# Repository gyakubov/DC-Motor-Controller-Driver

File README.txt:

DC Motor Controller & Driver README
===================================

This directory has the open source DC Motor Controller & Driver software, board layouts, schematics, and parts list.

For the latest updates by the original author of this project visit:
http://morgandemers.com/?page_id=444

Author: Morgan Demers

+---------+
| LICENSE |
+---------+

This work is licensed under the Creative Commons Attribution-NonCommercial-ShareAlike 3.0 Unported License. To view a copy of this license, visit http://creativecommons.org/licenses/by-nc-sa/3.0/.

+--------------+
| Introduction |
+--------------+

In the winter of 2009 I began working on a Gingery Style metal lathe, as an alternative to buying a chinese made 7x12. It was my desire to attain some casting and machining skills, and in the end to have a lathe with similar capabilities. The original Gingery design calls for cone pulleys and belt changes to get varying speeds with no compensation for load. As I have a background in Computer Engineering, I thought it would be a great opportunity to design a Controller & Driver for a 2hp DC Treadmill Motor for the Lathe. I also wanted a fairly nice & simple digital interface that I could use to control the machine tool. And thus in 2011 I began working on the electronics / software aspect of the project. It is now 2013, my lathe is built, and the Controller, Driver and Software fairly well tested. It has been my end goal to make the project available to anyone who is interested in building a similar Controller for their own machine tool ( this can be used on a lathe, milling machine, drill press, etc... ).

+--------------+
| Dependencies |
+--------------+

Software:

The software was written for the Microchip PIC18LF14K50 Microcontroller, and was developed in the MPLAB v8.76 IDE for the Microchip C18 compiler ( free / lite version ). It may be possible to use MPLAB X, however I have not tested it yet...

I use a PICkit2 to program the Controller. I'd imagine a PICkit3 would work fine as well...

Hardware:

The Board Layouts & Schematics are all done in the free / lite version of Eagle 6.1.0. 

+---------------+
| Prerequisites |
+---------------+

In order to build the Controller / Driver you will need some skills / tools. You should have some experience with etching your own printed circuit boards, soldering on components, etc... I've made a point to not use SMD components to make it a bit easier for those who might have through-hole experience, but not SMD...

To get the software onto the controller you will need a PICkit2 ( or PICkit3 ) programmer. At the very least you will need the PICkit2 programmer software to install the 'hex' file in the Sofware Directory, or you will need the MPLAB IDE with C18 compiler installed to build the project and program the Controller.

To print the board layouts you will need Eagle v6.1.0 ( or newer ).

I've made a point to design the Controller / Driver within the limitations of the free versions of MPLAB IDE, C18 Compiter, Eagle v6.1.0, and thus you should not have to buy any software to get this project to work.

+---------------------+
| Directories & Files |
+---------------------+

LICENSE.txt - contains the license for this piece of software & hardware. Please read, open source though not for commercial use. If making modifications maintain changelog, and please leave the names of prior authors, and url to original source ( http://morgandemers.com/?page_id=444 )

README.txt - this file

Parts_List.xls - Excel Spreadsheet of all the parts required to build the Controller / Driver / Interface

Parts_List.csv - CSV version of Excel Sheet if you don't have Excel

'Software' folder - Contains the PIC18LF14K50 C18 software for the Controller. Load MPLAB v8.76 project file, or you can find pre-compiled HEX file that you could download directly to the Controller board.

'Hardware' folder - Contains all Eagle v6.1.0 Schematics & Board Layouts for this project

'Hardware/Eagle Libraries' folder - Contains any Eagle Library dependencies - only used for QRD1114 part in 'Tachometer' schematic / board.

'Hardware/Photos' folder - Contains some photos of my controller / boards / etc... A bit weak but thought it would be relevant to include some photos.

Hardware/Controller.{sch|brd} - Controller Schematic / Board.

Hardware/Driver.{sch|brd} - Driver Schematic / Board.

Hardware/Tachometer.{sch|brd} - Tachometer Schematic / Board.

Hardware/120VAC.sch - Mains 120VAC connection to Driver Schematic

Hardware/Motor.sch - Connections from Motor to Forward/Reverse Relay to Driver Schematic

Hardware/LCD.sch - Connections from LCD to 2x8_to_1x16 board to 1x16_to_1x16 board to Controller Schematic

Hardware/Interface.sch - Connections from 3 interface buttons and RPM potentiometer to 1x9_to_1x9 board to Controller Schematic

'Encoder Wheels' folder - Contains some sample pdf files of Encoder Wheels that you can print out. I would also recommend you download this encoder wheel software that I currently use to create all my wheels at this point - http://code.google.com/p/wheel-encoder-generator/

+-------------------------+
| Putting It All Together |
+-------------------------+

At some point I may produce a video tutorial of building the controller, driver boards, programming the controller, and hooking everything up to a treadmill motor. That being said, it hasn't been done yet, though you can follow the steps below to get an idea of how to go about building the Controller / Driver.

The Circuit Boards were all made at home using the Toner Transfer Method. I've had fairly good success with Staples Photo Basic Gloss paper and a cheap Laminator that I purchased at Costco. I use Ferric Chloride to etch my boards, and have had no problem doing so. I have recently become aware that the 'Staples Photo Basic Gloss' paper is no longer available, but similar results should be capable when using a Glossy Color Laser paper.

Some suggestions:

i. Heatshrink tubing is a great way to insulate all high voltage wires.
ii. 1/4" Quick Disconnect Connectors work well for 120VAC & Motor Connections ( my treadmill motor came with 1/4" quick disconnects ).

Step 1: LCD
-----------
*refer to LCD.sch, 2x8_to_1x16.{sch|brd}, 1x16_to_1x16.{sch|brd} in Hardware folder for details

a. Start by soldering on the 2-1x8 female headers ( if you purchased the LCD display with the 2x8 solder pads ).

b. Make a 2x8_to_1x16 PCB. You should cut a sufficient length of 16 conductor ribbon cable and solder one end to the 2x8_to_1x16 PCB. The 2x8 male pins will connect directly onto the LCD's female header that you soldered in (a) ( take a look at Hardware/Photos to get an idea of how this looks ).

c. Make a 1x16_to_1x16 PCB. Solder the other end of the ribbon cable to the solder pads on the 1x16_to_1x16 PCB. You will solder on a 1x16 male pin header which will connect to the Controller.

Step 2: Interface
-----------------
*refer to Interface.sch, 1x9_to_1x9.{sch|brd} in Hardware folder for details

a. Make a 1x9_to_1x9 PCB. Make note of the Interface Component positions from the Interface.sch. I'll repeat here for clarity - Pins {1,2} connect to Right Button ( SPST momentary push button - NO ), Pins {3,4} connect to Menu Button ( SPST momentary push button - NO ), Pins {5,6} connect to Left Button ( SPST momentary push button - NO ), Pins {7,8,9} connect to RPM Adjustment Precision Potentiometer ( 5k, Multi-Turn ) - Pin 7 = Ground, Pin 8 = V+, Pin 9 = Variable Pot Voltage.

b. Solder a 1x9 male pin header to the other end of the 1x9_to_1x9 PCB, this will connect to the Controller's 'INTERFACE' header.

Step 3: Controller
------------------
*refer to Controller.{sch|brd} in Hardware folder for details

a. Make the 'Controller' PCB, and solder on the components - Do not insert M1 ( PIC18LF14K50 ) until you do (d) below...

b. Connect the Interface 1x9_to_1x9 PCB to the 'INTERFACE' female header on the Controller.

c. Connect the 1x16_to_1x16 PCB to the 'LCD' female header on the Controller.

d. Connect +5V power to POWER terminal block, hook a multimeter up to VTEST, and adjust P1 until you get 3.4V ( *only if using a PIC18LF... )

e. Turn off +5V power, insert M1 ( PIC18LF14K50 )

f. Connect PICKIT2, Load MPLAB or PICKIT2 Programmer Software. PIC18LF14K50 should be detected.

g. Load the 'DC Motor Controller' software into MPLAB, and Program the PIC18LF14K50

h. Once programmed, disconnect the PICKIT2, LCD should show welcome message ( might have to cycle power first )

i. If 'welcome message' displayed, and now on 'RPM: 0','TRG: ...' menu, test the Interface Buttons, otherwise you will have to debug the Controller Board - possibly bad trace, connection, or misplaced components...

*How to use the interface - Menu Button rotates between sub-menus, and Holding the Menu Buttons and pressing Left or Right will change the main menu. Left and Right buttons alone either increment or decrement menu items, or do other actions as suggested on the LCD ( such as start or stop the motor ).

j. Connect your multimeter to the VTEST ( ground pin ) and the PWM Out pin of the 'DRIVER_OUT' header. On the main menu, set the RPM with the RPM Potentiometer, and then press the 'Left Button' to start the motor. You should see a change in voltage on the multimeter. If you have a Frequency measurement feature, use that to verify the 25khz frequency.

Step 4: Tachometer
------------------
*refer to Tachometer.{sch|brd} in Hardware folder for details

a. Make the 'Tachometer' PCB, and solder on the components. This board is a bit tricky, as it has 2 boards in 1 - you will cut off the smaller board that has the QRD1114, and then solder that board onto the main board such that the QRD1114 is facing outward ( toward the encoder wheel, at least in my setup ).

b. You can cut out a set of 3 conductors from your 16 conductor ribbon cable for the Tachometer cable. Using the 3-pin Molex .100 ( 2.54mm ) KK crimp terminals & housings, create a cable to connect the Tachometer to the Controller via the 'TACH' Male Header.

c. Using a laser printer ( or inkjet, then copied on a laser copier ) print out '16_transistion.pdf' from the 'Encoder Wheels' folder.

d. Connect the Tachometer to the Controller, and then move the encoder wheel printout from (c) in front of the QRD1114 sensor ( needs to be very close to the encoder 1/8" or less ). While transitioning between black & white monitor the LCD to see if the RPM changes at all. You can also go to the second menu ( HOLD Menu and press the Right Button ), then the 3rd sub_menu ( press Menu 3 times ). It should have 'TRG: ..' and 'ENC: ..' displayed. While moving the wheel in front of the sensor you should see the ENC number change ( that is what it is seeing on the encoder in a given sample ).

Step 5: Driver
--------------
*refer to Driver.{sch|brd}, Motor.sch in Hardware folder for details

a. Make the 'Driver' PCB, and solder on the components. Note that AC1, AC2, M+, M- are wire pads, and should have 16 gauge wire soldered in and connected to fully insulated quick disconnect connectors on the other end ( for hooking up to 120VAC & Motor ).

b. You can cut out a set of 5 conductors from your 16 conductor ribbon cable for the Driver cable. Using the 5-pin Molex .100 ( 2.54mm ) KK crimp terminals & housings, create a cable to connect the Driver to the Controller via the 'DRIVER_IN' Male Header.

c. Connect either regulated +12V to POWER_IN ( and short 12VREG ) or connect unregulated +12V-30V to POWER_IN and adjust POT1 until voltage at FAN1 is +12V. You should see the white indicator LED ( LED3 ) turn on with power. When a PWM signal is present from the Controller, you should also see the 'Green' indicator LED ( LED1 ) illuminate ( though brightness will vary depending on the DUTY cycle of the PWM signal ).

d. You can cut out a set of 2 conductors from your 16 conductor ribbon cable for the Relay cable. Using the 2-pin Molex .100 ( 2.54mm ) KK crimp terminals & housings, create a cable to connect the Driver to the Relay ( which is used to reverse the motor ). The 'relay' end of the cable should be soldered to a 1/4" fully insulated female quick disconnects which can be put directly onto the relay drive plug pins. To see how you should connect the Motor to the Relay to the Driver refer to Motor.sch.

e. To set the current at which the 'Current Limit' will trip, hook up your multimeter to pins 3 & 4 of IC1, and adjust 'CSENSE_ADJUST' until voltage matches that of expected voltage across current sensing resistor 'RSENSE'. I use a 0.01ohm current sense resistor, so for a 10A current limit, set 'CSENSE_ADJUST' such that the voltage across pins 3 & 4 of IC1 is 0.1V. If your multimeter is not that sensitive, you can measure the resistance of the 'CSENSE_ADJUST' pot on the same pins. Since you know we are working with a +12V supply, you can use the voltage divider equation ( Vout = Vin*(R2/(R1+R2)) ) to determine the resistance at pins 3 & 4 such that the voltage across it would be 0.1V - for our 10A example, since the pot is a 5k and the upper leg is tied to a 22k resistor, you would do something like 0.1V = 12V*(R2/(22k+5k)) - solving for R2, you get R2 = ~225ohm.

f. To test the reverse relay, connect the relay via the 2 conductor cable made in (d) to the Driver, and on the Interface from the main menu ( when you first start up ) press the 'Menu Button' once. You should see the direction of rotation listed with the option to reverse, press the 'Left Button' to do that. You should hear the relay click, if it does that is ready to go.

Step 6: Testing on Low Voltage Motor
------------------------------------
a. It is best to test the setup out on a low voltage motor ( +12V preferrably ). You will have to bypass the bridge rectifier, and you can easily do this by connecting the lower drive voltage to the output pins of the rectifier with aligator clips, or micro clips. Once done, hookup the smaller motor to the M+, M- board wires. You should fashion a simple motor mount out of wood, and a means of affixing a small encoder wheel to the motor shaft ( I used hot glue - put a glob on the back of the wheel, and then press the motor shaft into the glob before it hardens ). You will have to mount the tachometer in such a way that it is positioned close enough to the wheel for a reading ( you could try and hold it by hand but would be difficult to maintain a consistent distance from the wheel ).

b. If you are not using a 96 transition encoder wheel for this test, you will need to hold down the 'Menu Button' and press the 'Right Button' until you get to the Encoder 'Resolution' menu. You can then use the left and right buttons to change the resolution of the encoder wheel. The setting is for transitions, not just black strips.

c. With the simple motor mount, encoder wheel on motor shaft, and tachometer positioned within 1/8" of the wheel you can proceed to set an RPM, and turn on the motor by pressing the 'Left Button' on the main menu. You should see the motor run and adjust such that RPM: and TRG: are the same. If the motor starts and runs at full speed, adjust the position of the Tachometer as it might be too far away, or too close to get a reading.

d. You can test the 'Reverse' capability by hooking the motor leads up to the 'Reverse Relay' and going to the 'Motor Direction' menu - second sub menu off the main menu. Press the 'Left Button' to switch directions.

Step 7: Testing on High Voltage Treadmill Motor
-----------------------------------------------
a. If everything tested successfully in 'Step 6', you can now test the Controller / Driver with the High Voltage Treadmill Motor. You should enclose the Driver within a grounded case of some sort ( I started off with a gutted ATX power supply ), though I have tested the circuit without it before ( standing some distance away with my hand on a power strip switch ). Caution must be taken as it is extremely dangerous working with a circuit that is connected to 120VAC. The 470uF capacitor will also hold a substantially dangerous charge after the power is removed, and even though there is a 200k bleeder, it takes a few minutes for the capacitor to drain - I have seen quite a few sparks when intentially shorting the terminals of the capacitor with an insulated screw driver, so be careful when you get to this point.

+-----------------------+
| Interface Menu System |
+-----------------------+

You navigate the menu system with Left, Right, and Menu Buttons. To change between 'Menus' you hold the 'Menu' button and press either 'Left' or 'Right' which will rotate forward or backward through the menus. If you go past the last menu, you will end up at the first and visa versa. To change between 'Sub Menus' you simply press the 'Menu' button.

On some menus the Left and Right buttons will increment / decrement a value.

On some menus either the Left or Right buttons will do some action as indicated.

############

Menu 1: Main

  Sub Menu 1 - RPM & RPM Target Display ( Main Menu )

  Sub Menu 2 - Motor Direction - Left Button for Forward or Reverse

  Sub Menu 3 - Indexer

Menu 2: Info

  Sub Menu 1 - Current & Last Sample Errors - ER0 = Current Error, ER1 = Last Error

  Sub Menu 2 - PWM Duty Cycle

  Sub Menu 3 - ( TRG: ) Target Setpoint vs. ( ENC: ) Last Sample

Menu 3: PID Algorithm Constants

  Sub Menu 1 - KP - Proportional Constant Numerator

  Sub Menu 2 - KP - Proportional Constant Denominator

  Sub Menu 3 - KI - Integral Constant Numerator

  Sub Menu 4 - KI - Integral Constant Denominator

  Sub Menu 5 - KD - Derivative Constant Numerator

  Sub Menu 6 - KD - Derivative Constant Denominator

  Sub Menu 7 - FF - Feed Forward Constant Numerator

  Sub Menu 8 - FF - Feed Forward Constant Denominator

Menu 4: Settings

  Sub Menu 1 - Max Duty

  Sub Menu 2 - Max RPM

  Sub Menu 3 - Encoder Resolution

+-----------------------+
| Tuning The Controller |
+-----------------------+

Depending on your particular motor, the PID constants will most likely be slightly different than my own for your own setup. There are quite a few good documents online on how to adjust the constants in order to get a fairly good response.

Setting up Feed Forward:

a. Turn off the PID constants by setting the numerators to 0.

b. Set a desired RPM - 200 or something like that.

c. Go to the Feed Forward Sub Menu, and increase the value until the RPM displayed matches that of your desired RPM target.

d. Increase the RPM via the RPM Adjustment Knob and see if the RPM displayed follows the change made.

* feed forward can be used exclusively for variable speed adjustment if no feedback / load compensation is required. It will help the PID algorithm to not have to work so hard to maintain speed if used in conjunction with KP, KI, KD.

Setting up the PID Constants:

a. Before doing this step you need a way to apply a load to the spindle - possibly by cutting some metal if you are setup for that. I have had ok success holding a blank spindle ( no tools, just the shaft ) with a welder's glove - I don't necessarily recommend this, but it seemed fairly safe when I was initially testing my controller.

b. With the spindle running at some desired RPM ( and hopefully Feed Forward setup to get to that speed without a load on the spindle ), go to the 'KP' sub menu and initially set it to 1/1. The proportional constant of the PID controller will simply apply Error*KP to the PID output ( duty cycle ). So this will give you an instantaneous boost in output from the motor to try and maintain speed.

c. Increase KP's constants until you get to a slight overshoot case where the motor will jump beyond the desired RPM when you load the spindle. Back off KP slightly.

d. Increase KD's constant to eliminate any overshoot and reduce the settling time. Be careful with KD ( mine is typically set to 2/30 or something like this ) as it will add instability to the system if too high. 

e. If you find you have a steady state error ( the system settles at an RPM other than the target ) or you are not getting a fast enough response you should increase KI.

*My current settings for a 2hp treadmill motor with 96 resolution encoder wheel - KP=2/1, KI=3/2, KD=2/30, FF=35/4.

Effects of increasing PID Constants on System:

KP will descrease rise time, increase overshoot, decrease steady state error

KI will decrease rise time, decrease overshoot, increase settling time, eliminate steady state error

KD will decrease overshoot, decrease settling time

+-----------------------+
| Spindle Indexing      |
+-----------------------+

This controller has the capability of indexing a spindle if the Tachometer and Reverse Relay is setup. Having the ability to accurately position a spindle can be of some benefit depending on what you are using the controller for. On a lathe for instance you could use it to cut graduated micrometer dials, or if you had a dremel holder for your toolpost, you could do some really interesting stuff...

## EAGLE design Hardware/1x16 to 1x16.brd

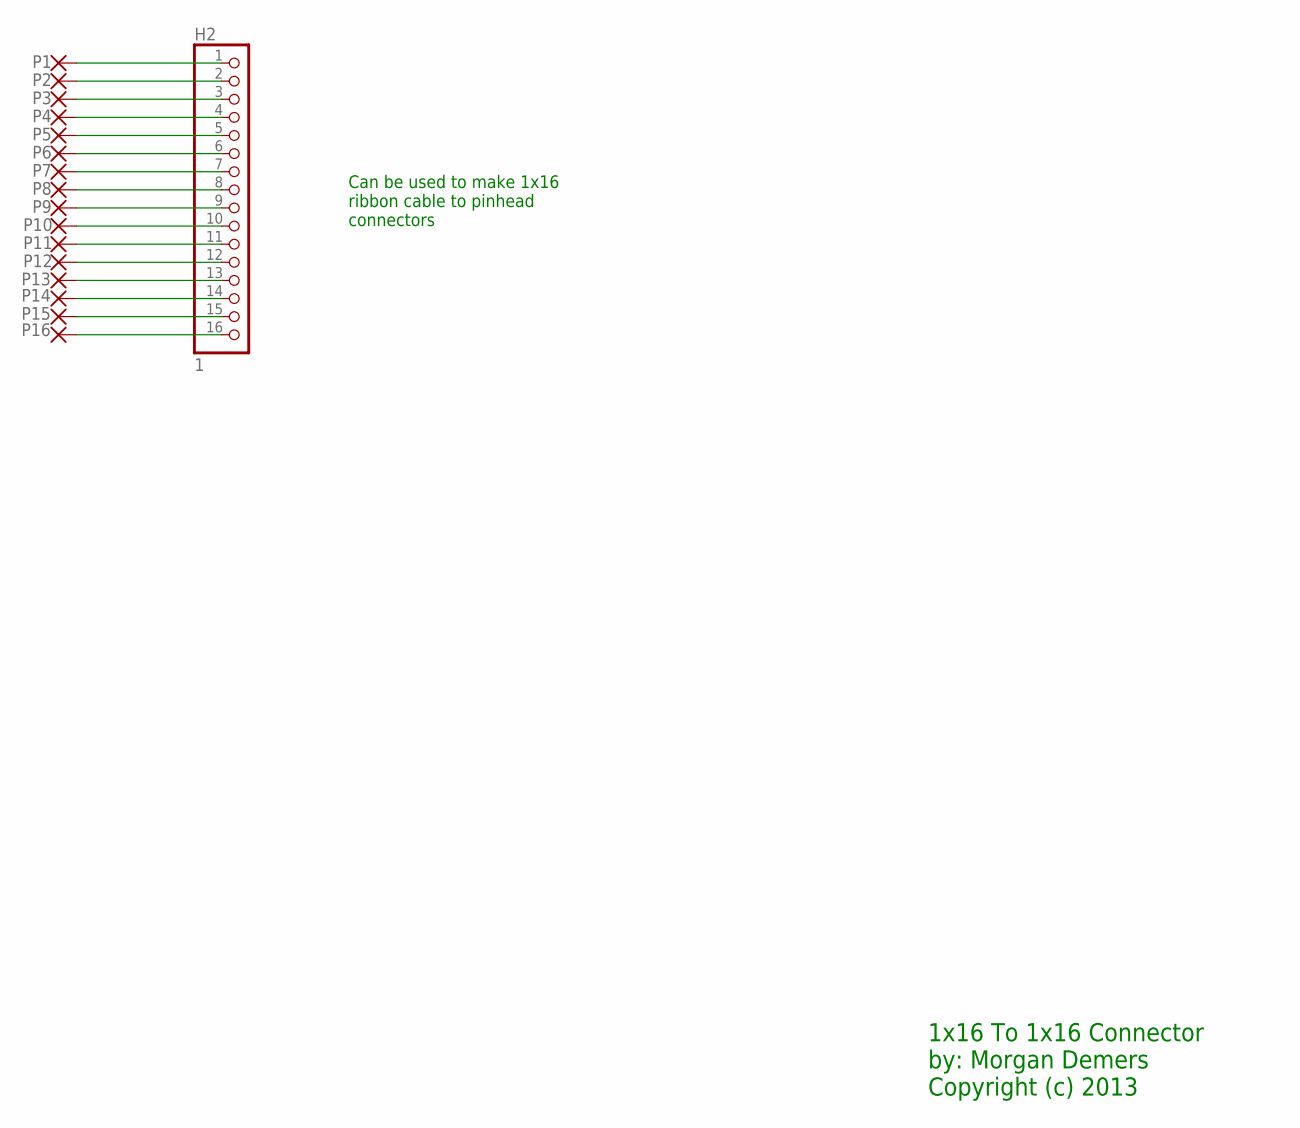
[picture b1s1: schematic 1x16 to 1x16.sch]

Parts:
H2: 1; 1X16
P1, P2, P3, P4, P5, P6, P7, P8, P9, P10, P11, P12, P13, P14, P15, P16: 1,6/0,9

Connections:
S$1: H2.1, P1.1
S$2: H2.2, P2.1
S$3: H2.3, P3.1
S$4: H2.4, P4.1
S$5: H2.5, P5.1
S$6: H2.6, P6.1
S$7: H2.7, P7.1
S$8: H2.8, P8.1
S$9: H2.9, P9.1
S$10: H2.10, P10.1
S$11: H2.11, P11.1
S$12: H2.12, P12.1
S$13: H2.13, P13.1
S$14: H2.14, P14.1
S$15: H2.15, P15.1
S$16: H2.16, P16.1

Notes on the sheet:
1x16 To 1x16 Connector by: Morgan Demers Copyright (c) 2013
Can be used to make 1x16 ribbon cable to pinhead connectors

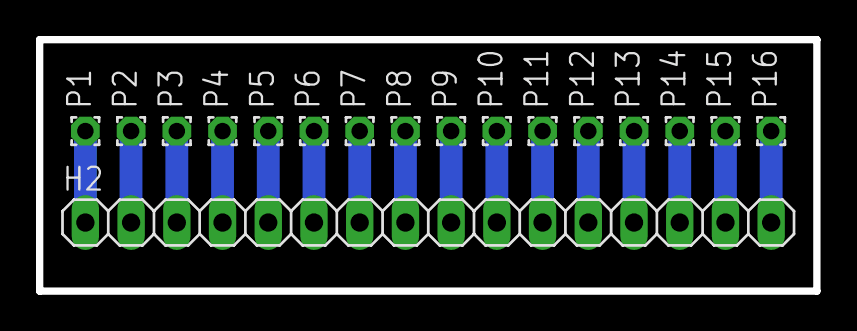
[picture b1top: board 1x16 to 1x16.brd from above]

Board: 2 copper layers, 43.2 x 14.0 mm, 17 parts (0 on the bottom side), 16 nets.

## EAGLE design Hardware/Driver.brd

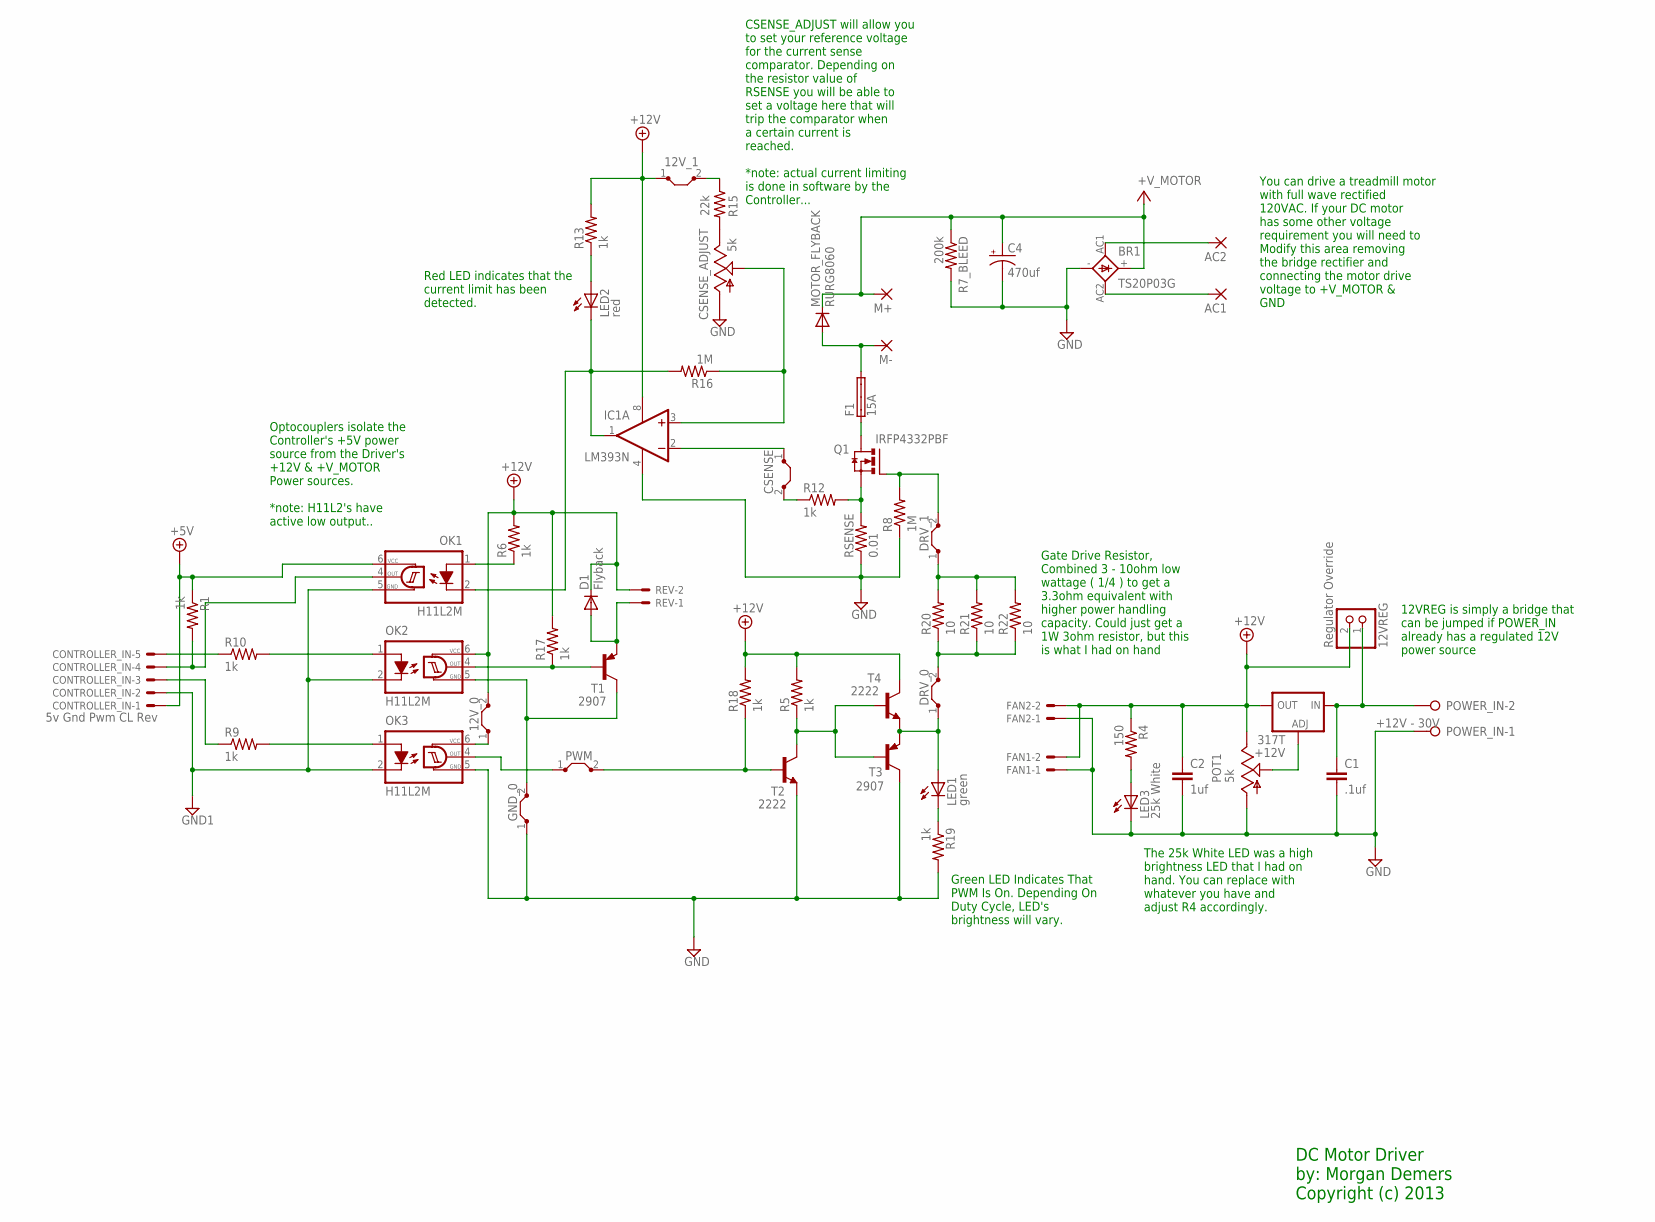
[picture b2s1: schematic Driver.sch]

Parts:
12VREG: Regulator Override; 1X02
12V_0: J10MM; 10
12V_1: J5MM; 05
317T: +12V; 317TS
AC1, AC2: WIREPAD4,16O1,6; 4,16O1,6
BR1: TS20P03G; FB32
C1: .1uf; C2.5-3
C2: 1uf; C2.5-3
C4: 470uf; EB22,5D
CONTROLLER_IN: 5v Gnd Pwm CL Rev; 22-23-2051
CSENSE: J7MM; 07
CSENSE_ADJUST: 5k; B25P
D1: Flyback; D-2.5
DRV_0: J5MM; 05
DRV_1: J12MM; 12
F1: 15A; SHK20L
FAN1, FAN2: 22-23-2021
GND_0: J7MM; 07
IC1: LM393N; DIL08
LED1: green; LED3MM
LED2: red; LED3MM
LED3: 25k White; LED3MM
M+: WIREPAD4,16O1,6; 4,16O1,6
M-: WIREPAD4,16O1,6; 4,16O1,6
MOTOR_FLYBACK: RURG8060; TO220ACS
OK1, OK2, OK3: H11L2M; DIL06
POT1: 5k; B25P
POWER_IN: +12V - 30V; W237-132
PWM: J5MM; 05
Q1: IRFP4332PBF; TO247BV
R1, R18: 1k; 0204/7
R4: 150; 0204V
R5, R6, R9, R10, R12, R13, R19: 1k; 0204V
R7_BLEED: 200k; 0207/10
R8: 1M; 0204V
R15: 22k; 0204V
R16: 1M; 0204/5
R17: 1k; 0204/5
R20, R21, R22: 10; 0204V
REV: 22-23-2021
RSENSE: 0.01; 0204V
T1, T3: 2907; TO92-CBE
T2, T4: 2222; TO92-EBC

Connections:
+5V: CONTROLLER_IN.1, OK1.6 (VCC), R1.1
+12V: 12VREG.2, 12V_0.2, 12V_1.1, 317T.2 (OUT), C2.1, D1.C, FAN1.2, FAN2.2, IC1.8 (V+), OK2.6 (VCC), POT1.E, R4.1, R5.2, R6.2, R13.2, R17.2, R18.2, REV.2, T4.C
GND: BR1.-, C1.2, C2.2, C4.-, CSENSE_ADJUST.A, FAN1.1, FAN2.1, GND_0.1, IC1.4 (V-), LED3.K (C), OK3.5 (GND), POT1.A, POWER_IN.1, R7_BLEED.2, R8.1, R19.2, RSENSE.1, T2.E, T3.C
GND1: CONTROLLER_IN.2, OK1.5 (GND), OK2.2 (C), OK3.2 (C)
unnamed: OK2.1 (A), R10.2
unnamed: OK3.4 (OUT), PWM.1
unnamed: CSENSE.1, IC1.2 (-IN)
S$1: CONTROLLER_IN.3, R9.1
S$2: PWM.2, R18.1, T2.B
S$4: Q1.S, R12.2, RSENSE.2
S$6: 317T.1 (ADJ), POT1.S
S$7: CONTROLLER_IN.5, R10.1
S$8: CONTROLLER_IN.4, OK1.4 (OUT), R1.2
S$9: R5.1, T2.C, T3.B, T4.B
S$10: 12V_1.2, R15.1
S$11: LED3.A, R4.2
S$12: IC1.1 (OUT), LED2.K (C), OK1.2 (C), R16.2
S$13: DRV_0.2, R20.1, R21.1, R22.1
S$14: OK2.4 (OUT), R17.1, T1.B
S$16: DRV_1.2, Q1.G, R8.2
S$20: F1.1A, Q1.D
S$21: AC1.1, BR1.AC2
S$22: OK1.1 (A), R6.1
S$23: AC2.1, BR1.AC1
S$25: F1.2A, M-.1, MOTOR_FLYBACK.A
S$26: 12V_0.1, OK3.6 (VCC)
S$27: CSENSE_ADJUST.E, R15.2
S$32: OK3.1 (A), R9.2
S$34: CSENSE.2, R12.1
S$45: CSENSE_ADJUST.S, IC1.3 (+IN), R16.1
S$50: LED1.K (C), R19.1
S$51: LED2.A, R13.1
S$52: DRV_1.1, R20.2, R21.2, R22.2
S$54: 12VREG.1, 317T.3 (IN), C1.1, POWER_IN.2
S$129: DRV_0.1, LED1.A, T3.E, T4.E
S$171: D1.A, REV.1, T1.E
S$448: GND_0.2, OK2.5 (GND), T1.C
V+: BR1.+, C4.+, M+.1, MOTOR_FLYBACK.C, R7_BLEED.1

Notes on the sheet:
Gate Drive Resistor, Combined 3 - 10ohm low wattage ( 1/4 ) to get a 3.3ohm equivalent with higher power handling capacity. Could just get a 1W 3ohm resistor, but this is what I had on hand
Green LED Indicates That PWM Is On. Depending On Duty Cycle, LED's brightness will vary.
12VREG is simply a bridge that can be jumped if POWER_IN already has a regulated 12V power source
Red LED indicates that the current limit has been detected.
You can drive a treadmill motor with full wave rectified 120VAC. If your DC motor has some other voltage requirement you will need to Modify this area removing the bridge rectifier and connecting the motor drive voltage to +V_MOTOR & GND
CSENSE_ADJUST will allow you to set your reference voltage for the current sense comparator. Depending on the resistor value of RSENSE you will be able to set a voltage here that will trip the comparator when a certain current is reached. *note: actual current limiting is done in software by the Co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
Optocouplers isolate the Controller's +5V power source from the Driver's +12V & +V_MOTOR Power sources. *note: H11L2's have active low output..
The 25k White LED was a high brightness LED that I had on hand. You can replace with whatever you have and adjust R4 accordingly.
DC Motor Driver by: Morgan Demers Copyright (c) 2013

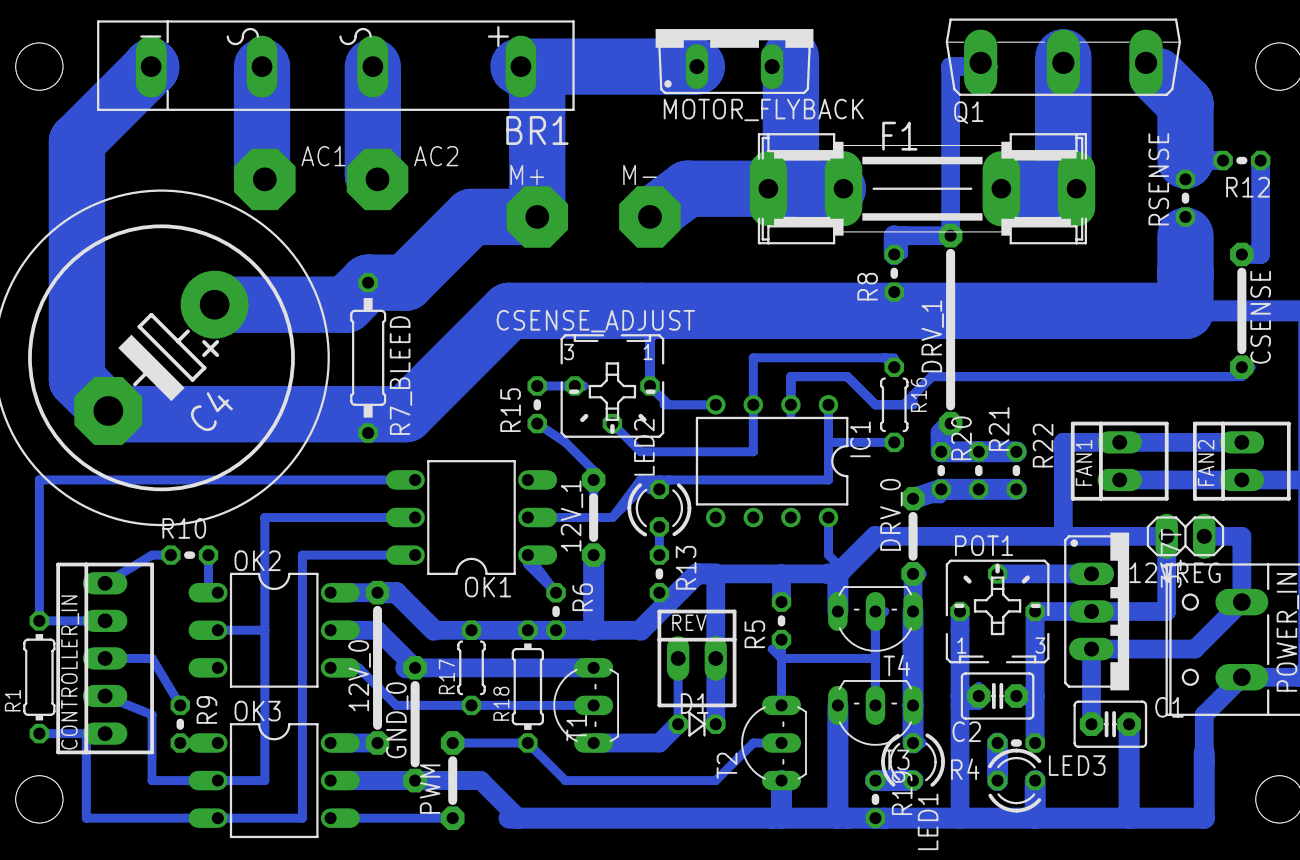
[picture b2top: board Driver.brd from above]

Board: 2 copper layers, 58 parts (0 on the bottom side), 38 nets.

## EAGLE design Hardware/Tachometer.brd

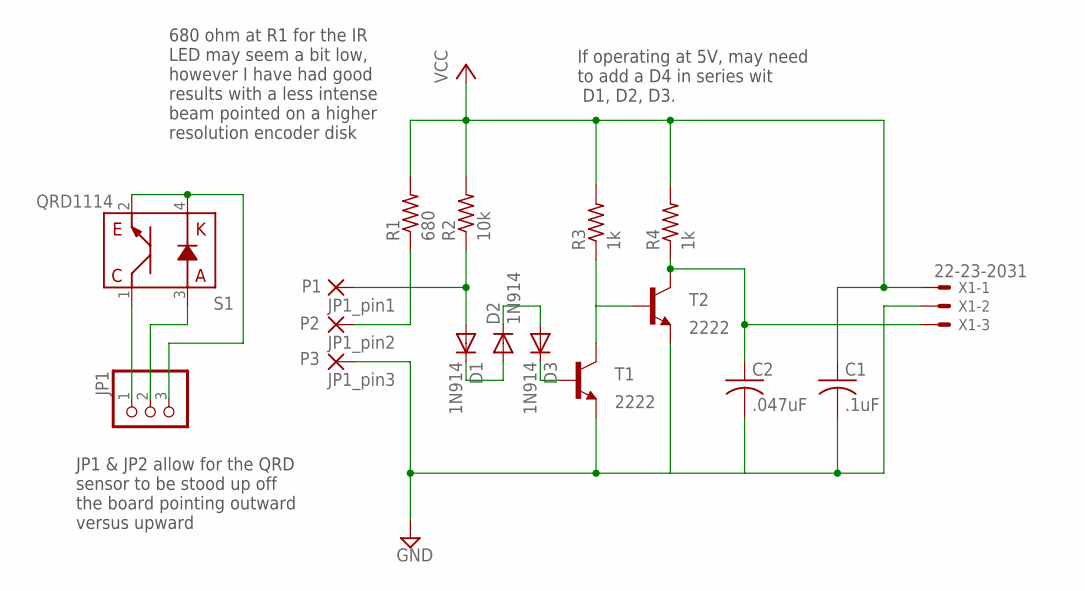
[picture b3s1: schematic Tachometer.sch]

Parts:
C1: .1uF; C025-024X044
C2: .047uF; C025-024X044
D1, D2, D3: 1N914; D-2.5
JP1: 1X03/90
P1: JP1_pin1; 1,6/0,9
P2: JP1_pin2; 1,6/0,9
P3: JP1_pin3; 1,6/0,9
R1: 680; 0204/5
R2: 10k; 0204/5
R3, R4: 1k; 0204/5
S1: QRD1114
T1, T2: 2222; TO92-EBC
X1: 22-23-2031

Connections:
GND: C1.2, C2.2, P3.1, T1.E, T2.E, X1.2
unnamed: D1.A, P1.1, R2.1
unnamed: R3.1, T1.C, T2.B
unnamed: JP1.3, S1.2 (C), S1.4 (K)
unnamed: JP1.2, S1.3 (A)
unnamed: JP1.1, S1.1 (E)
unnamed: P2.1, R1.1
unnamed: D1.C, D2.A
unnamed: D2.C, D3.A
unnamed: D3.C, T1.B
unnamed: C2.1, R4.1, T2.C, X1.3
VCC: C1.1, R1.2, R2.2, R3.2, R4.2, X1.1

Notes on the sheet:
JP1 & JP2 allow for the QRD sensor to be stood up off the board pointing outward versus upward
680 ohm at R1 for the IR LED may seem a bit low, however I have had good results with a less intense beam pointed on a higher resolution encoder disk
If operating at 5V, may need to add a D4 in series wit D1, D2, D3.

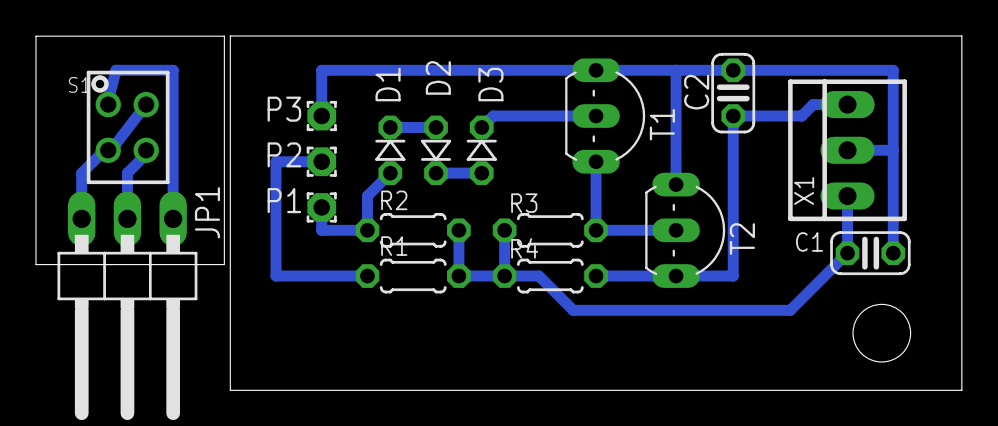
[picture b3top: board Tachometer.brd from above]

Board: 2 copper layers, 51.4 x 19.7 mm, 17 parts (0 on the bottom side), 12 nets.

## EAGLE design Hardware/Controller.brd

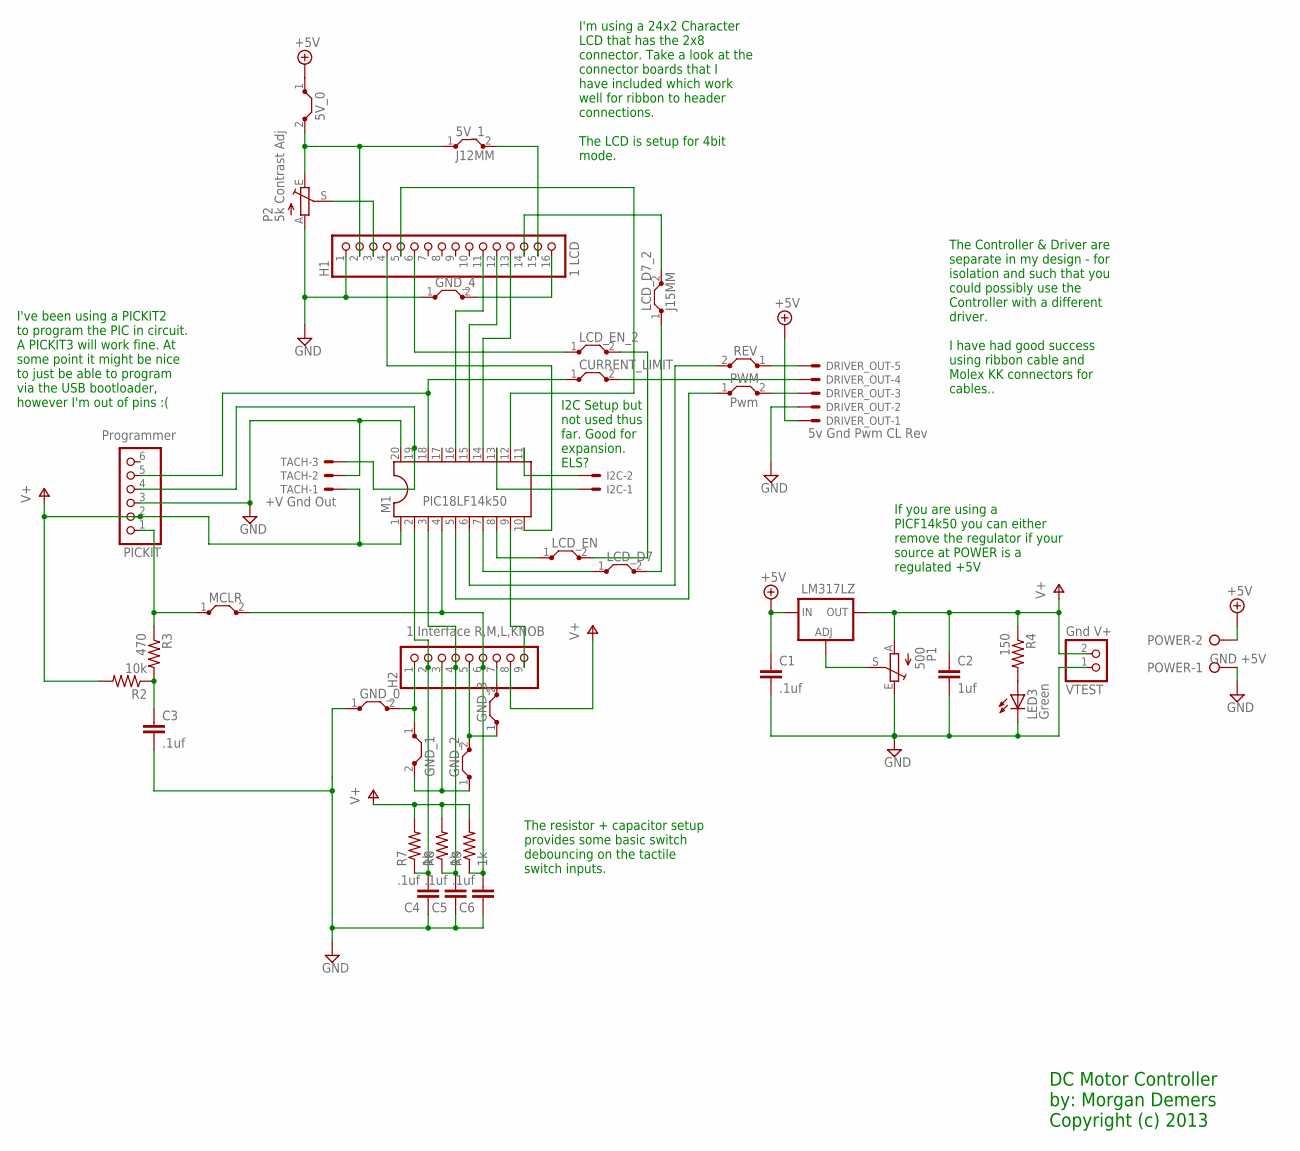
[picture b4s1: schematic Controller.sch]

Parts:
5V_0: J5MM; 05
5V_1: J12MM; 12
C1, C3: .1uf; C2.5-3
C2: 1uf; C2.5-3
C4, C5, C6: .1uf; C5B2.5
CURRENT_LIMIT: J30MM; 30
DRIVER_OUT: 5v Gnd Pwm CL Rev; 22-23-2051
GND_0, GND_4: J10MM; 10
GND_1, GND_2, GND_3: J5MM; 05
H1: 1 LCD; 1X16
H2: 1 Interface R,M,L,KNOB; 1X09
I2C: 22-23-2021
LCD_D7: J7MM; 07
LCD_D7_2: J15MM; 15
LCD_EN: J7MM; 07
LCD_EN_2: J7MM; 07
LED3: Green; LSU260
LM317LZ: 317L
M1: PIC18LF14k50; DIL20
MCLR: J15MM; 15
P1: 500; B25P
P2: 5k Contrast Adj; B25P
PICKIT: Programmer; 1X06/90
POWER: GND +5V; W237-132
PWM: Pwm; 07
R2: 10k; 0204V
R3: 470; 0204V
R4: 150; 0204V
R7, R8, R9: 1k; 0204V
REV: J10MM; 10
TACH: +V Gnd Out; 22-23-2031
VTEST: Gnd V+; 1X02

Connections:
+5V: 5V_0.1, C1.1, DRIVER_OUT.1, LM317LZ.3 (IN), POWER.2
+5V_J0: 5V_0.2, 5V_1.1, H1.2, P2.E
GND: C1.2, C2.2, C3.2, C4.1, C5.1, C6.1, DRIVER_OUT.2, GND_0.1, GND_4.1, H1.1, LED3.K (C), M1.20, P1.E, P2.A, PICKIT.3, POWER.1, TACH.2, VTEST.1
GND_J0: GND_0.2, GND_1.1, H2.1
GND_J1: GND_1.2, GND_2.1, H2.3
GND_J3: GND_2.2, GND_3.1, H2.5
GND_J4: GND_3.2, H2.7
LMADJ: LM317LZ.1 (ADJ), P1.S
unnamed: 5V_1.2, H1.15
unnamed: LED3.A, R4.2
unnamed: GND_4.2, H1.16
S$2: MCLR.1, PICKIT.1, R3.1
S$3: I2C.2, M1.11
S$4: H2.9, M1.9
S$5: H1.3, P2.S
S$6: H1.14, LCD_D7_2.2
S$7: H1.6, LCD_EN_2.1
S$8: H1.4, M1.10
S$9: LCD_EN.2, LCD_EN_2.2
S$14: H1.5, M1.12
S$16: C4.2, H2.2, M1.2, R7.1
S$18: C3.1, R2.1, R3.2
S$19: H1.11, M1.16
S$20: LCD_EN.1, M1.8
S$21: H1.12, M1.15
S$22: H1.13, M1.14
S$23: M1.19, PICKIT.4, TACH.3
S$24: LCD_D7.1, M1.7
S$25: CURRENT_LIMIT.1, M1.18, PICKIT.5
S$26: C5.2, H2.4, M1.3, R8.1
S$27: LCD_D7.2, LCD_D7_2.1
S$30: M1.6, REV.2
S$31: I2C.1, M1.13
S$32: C6.2, H2.6, M1.4, MCLR.2, R9.1
S$34: M1.5, PWM.1
S$39: DRIVER_OUT.5, REV.1
S$40: CURRENT_LIMIT.2, DRIVER_OUT.4
S$41: DRIVER_OUT.3, PWM.2
V+: C2.1, H2.8, LM317LZ.2 (OUT), M1.1, P1.A, PICKIT.2, R2.2, R4.1, R7.2, R8.2, R9.2, TACH.1, VTEST.2

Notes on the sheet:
I've been using a PICKIT2 to program the PIC in circuit. A PICKIT3 will work fine. At some point it might be nice to just be able to program via the USB bootloader, however I'm out of pins :(
If you are using a PICF14k50 you can either remove the regulator if your source at POWER is a regulated +5V
The Controller & Driver are separate in my design - for isolation and such that you could possibly use the Controller with a different driver. I have had good success using ribbon cable and Molex KK connectors for cables..
The resistor + capacitor setup provides some basic switch debouncing on the tactile switch inputs.
I'm using a 24x2 Character LCD that has the 2x8 connector. Take a look at the connector boards that I have included which work well for ribbon to header connections. The LCD is setup for 4bit mode.
I2C Setup but not used thus far. Good for expansion. ELS?
DC Motor Controller by: Morgan Demers Copyright (c) 2013

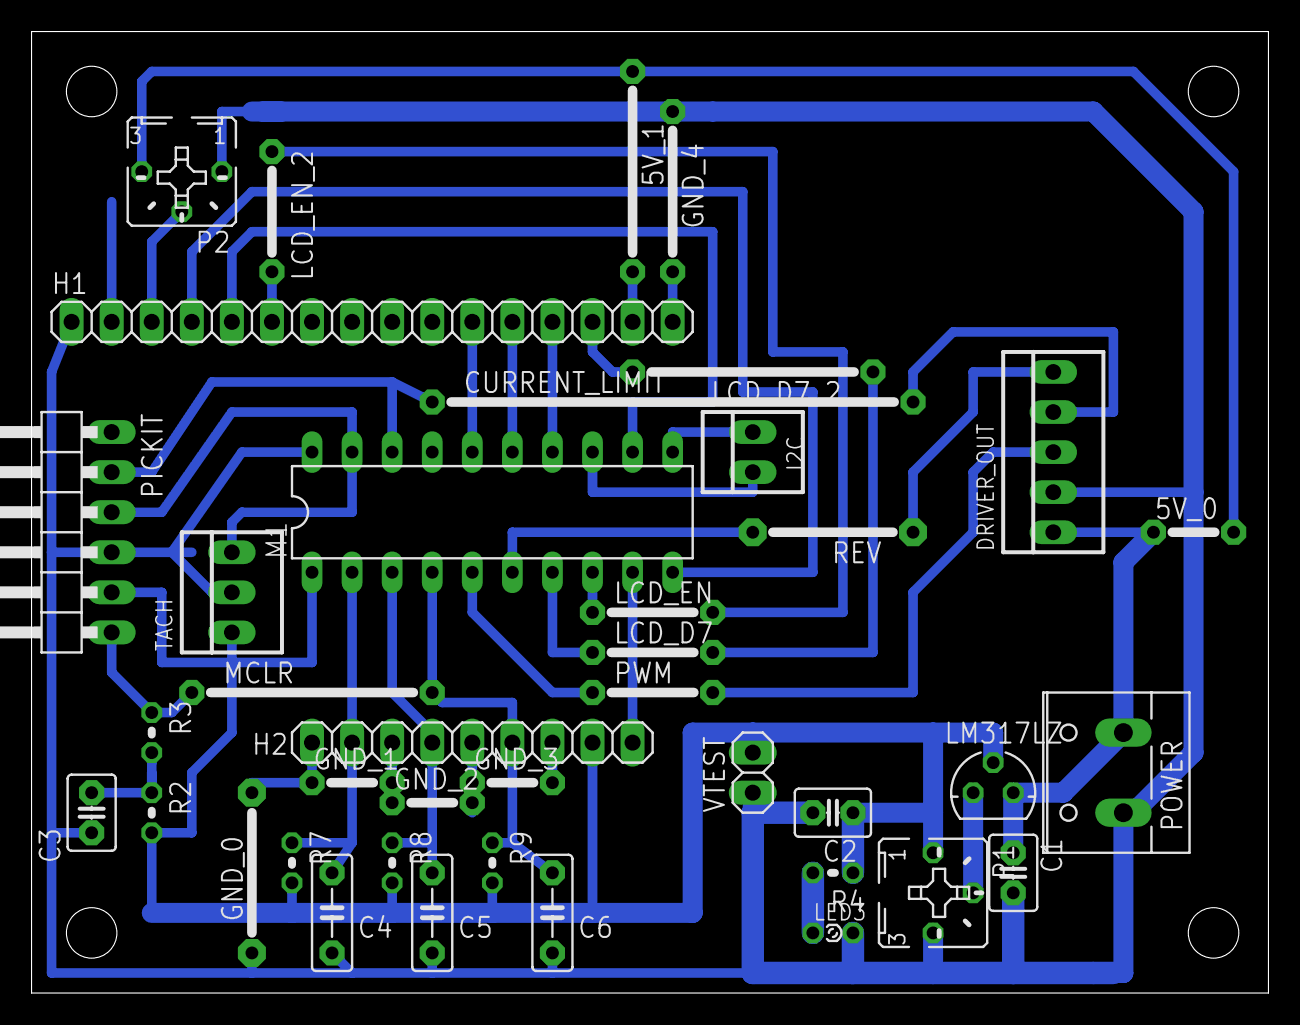
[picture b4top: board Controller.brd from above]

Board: 2 copper layers, 78.4 x 61.0 mm, 40 parts (0 on the bottom side), 39 nets.

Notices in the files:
parts and their libraries:
SparkFun-Sensors: Licensing: CC v3.0 Share-Alike You are welcome to use this library for commercial purposes.
